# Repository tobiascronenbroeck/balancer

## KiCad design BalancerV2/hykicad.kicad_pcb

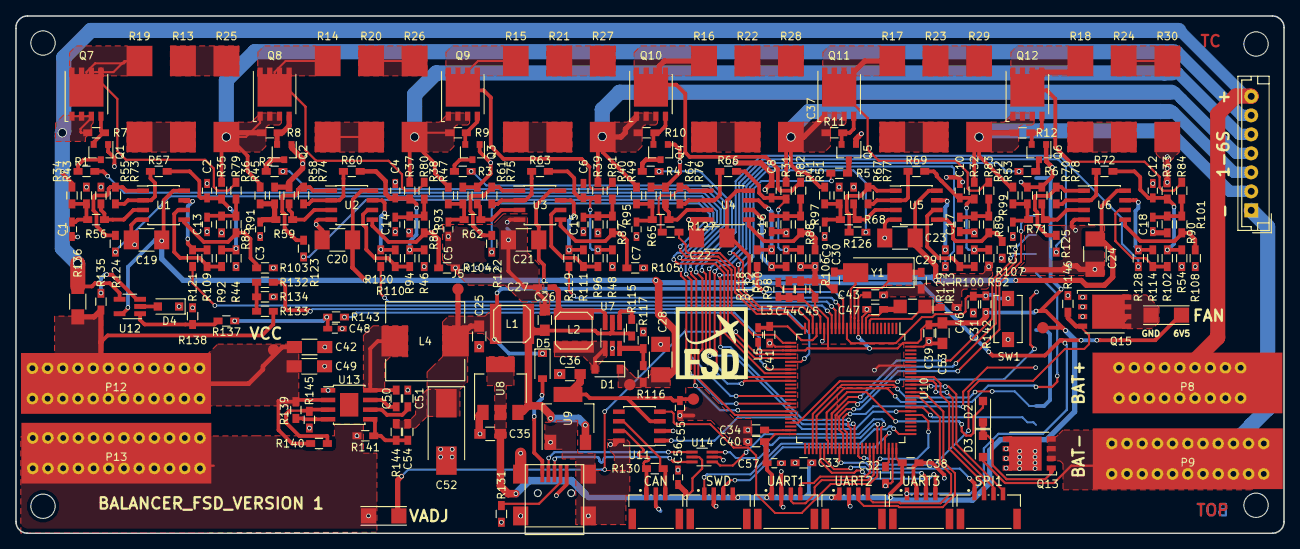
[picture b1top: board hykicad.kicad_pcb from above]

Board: 2 copper layers, 166.9 x 68.1 mm, 264 parts (1 on the bottom side), 177 nets.

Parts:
32.768kHz1: Crystal_Small; Crystal_SMD_MicroCrystal_CC7V-T1A-2pin_3.2x1.5mm_HandSolder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
C1, C2, C3, C4, C5, C6, C7, C8, C9, C10, C11, C12, C13, C14, C15, C16, C17, C18, C27, C48, C55, C56, C57: 100nF; C_0603_HandSoldering
C19, C20, C21, C22, C23, C24, C28: 2.2uF 100V; C_1210_HandSoldering
C25, C26, C35, C36, C53: 4,7uF 16V; R_0805_HandSoldering
C29, C30, C46, C47: 18pF; R_0603_HandSoldering
C31, C33, C34, C37, C38, C39, C40, C41, C43, C45: 100nF; R_0603_HandSoldering
C32: 10uF; R_0603_HandSoldering
C42: 4.7uF 100V X7S; C_1206_HandSoldering
C44: 1uF; R_0603_HandSoldering
C49: 0.1uF 100V X7R; C_1206_HandSoldering
C50: 0.01uF 50V; R_0603_HandSoldering
C51: 1uF 50V; R_0603_HandSoldering
C52: Tantal 100uF 10V; CP_Tantalum_Case-V_EIA-7343-20_Hand
C54: 3.3nF 50V; R_0603_HandSoldering
D1, D5: D; D_SOD-123
D2, D3, D4: D_Schottky; D_SOD-123F
J1, J2, J3, J4, J5: CONN_01X01; Measurement_Point_Round-SMD-Pad_Small
L1, L2: 100uH/4818/0.4A; SELF-WE-TPC_M
L3, L5: 1uH 750mA; C_0603_HandSoldering
L4: 330uF 690mA; Inductor_Wurth_HCI-1040
P1: USB_OTG; USB_Mini-B
P2: CONN_01X03; pel_molex-CM-502386-03
P3, P4, P5, P6, P11: CONN_01X04; pel_molex-CM-502386-04
P7: CONN_01X07; JST_EH_B07B-EH-A_07x2.50mm_Straight
P8: BAT+; 4mmHorizontal
P9, P13: GND; 4mmHorizontal
P10: CONN_01X14; FPC_14
P12: VCC; 4mmHorizontal
P14, P15: CONN_01X02; FPC_2
Q1, Q2, Q3, Q4, Q5, Q6: BC846; SOT-23
Q7, Q8, Q9, Q10, Q11, Q12: PMOS_TDSON; TDSON-8-1_HandSoldering
Q13, Q15: NMOS_TDSON; TDSON-8-1_HandSoldering
R1, R2, R3, R4, R5, R6: 3,3k; R_0603_HandSoldering
R7, R8, R9, R10, R11, R12: 47k; R_0603_HandSoldering
R13, R14, R15, R16, R17, R18, R19, R20, R21, R22, R23, R24, R25, R26, R27, R28, R29, R30: 1R2; SM_3 Pad
R31, R32, R33, R34, R35, R36, R37, R38, R39, R40, R41, R42, R43, R44, R45, R46, R47, R48, R49, R50, R51, R52, R53, R54, R79, R80, R81, R82, R83, R84, R85, R86, R87, R88, R89, R90, R127, R134: 100K; R_0603_HandSoldering
R55, R56, R57, R58, R59, R60, R61, R62, R63, R64, R65, R66, R67, R68, R69, R70, R71, R72, R73, R74, R75, R76, R77, R78, R91, R92, R93, R94, R95, R96, R97, R98, R99, R100, R101, R102, R103, R104, R105, R106, R107, R108, R109, R110, R111, R112, R113, R114, R115, R118, R119, R120, R121, R122, R123, R124, R125, R126, R128, R129, R132, R133, R137, R142, R143, R146: 10K; R_0603_HandSoldering
R116: 123K; R_0603_HandSoldering
R117: 5K1; R_0603_HandSoldering
R130: 120R; R_0603_HandSoldering
R131: OTG Jumper; R_0603_HandSoldering
R135: 100R; R_0603_HandSoldering
R136: 5mR; R_1206_HandSoldering
R138: 5K; R_0603_HandSoldering
R139: 221K; R_0603_HandSoldering
R140: 51.1K; R_0603_HandSoldering
R141: 2.37k; R_0603_HandSoldering
R144: 10k; R_0603_HandSoldering
R145: 10.7K; R_0603_HandSoldering
SW1: SW_PUSH_SMALL_H; SW_SPST_EVQPE1
U1, U2, U3, U4, U5, U6: LM358; SOIC-8_3.9x4.9mm_Pitch1.27mm
U7: MP3216DJ-LF-Z; TSOT-23-6_MK06A_HandSoldering
U8: AP111733; SOT-223
U9: AP111750; SOT-223
U10: STM32F407VGTx; LQFP-100_14x14mm_Pitch0.5mm
U11: TJA1051T; SOIC-8_3.9x4.9mm_Pitch1.27mm
U12: LT6106; SOT-23-5_HandSoldering
U13: LM5017MR; TI_SO-PowerPAD-8
U14: NUF2221W1T2G; SOT-363_SC-70-6_Handsoldering
Y1: 8MHz; Crystal_SMD_0603-2pin_6.0x3.5mm_HandSoldering

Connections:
6,5V: C25.1, C52.1, C54.2, D5.1, J5.1, L1.1, L4.2, P6.1, P14.2, R144.1
32V: C19.1, C20.1, C21.1, C22.1, C23.1, C24.1, C28.1, D1.1, J1.1, R116.2, U1.8, U2.8, U3.8, U4.8, U5.8, U6.8, U12.5
+3V3: C33.1, C35.1, C37.1, C38.1, C39.1, C40.1, C43.2, C53.1, C56.1, C57.1, J4.1, L3.1, L5.1, P3.4, P4.1, P5.1, P10.1, P10.8, R142.1, U8.2, U8.4, U10.11, U10.19, U10.28, U10.50, U10.75, U10.100, U14.5
+5V: C36.1, C55.2, J3.1, U9.4, U11.3
BAT-: D3.2, P7.1, P9.1, Q13.2, Q13.3, Q13.4
CANuC+: P2.1, R130.1, U11.7
CANuC-: P2.3, R130.2, U11.6
CELL1: P7.2, Q12.1, Q12.2, Q12.3, R12.1, R29.1, R32.2, R42.2
CELL2: P7.3, Q11.1, Q11.2, Q11.3, R11.1, R28.1, R31.2, R41.2
CELL3: P7.4, Q10.1, Q10.2, Q10.3, R10.1, R27.1, R39.2, R40.2
CELL4: P7.5, Q9.1, Q9.2, Q9.3, R9.1, R26.1, R37.2, R38.2
CELL5: P7.6, Q8.1, Q8.2, Q8.3, R8.1, R25.1, R35.2, R36.2
CELL6: P7.7, P8.1, Q7.1, Q7.2, Q7.3, R7.1, R34.2, R136.2, U12.4
CS_LCD: P10.3, U10.61
CS_SD: P11.1, U10.60
CS_TOUCH: P10.11, U10.62
Cell1PWM: R1.2, U10.40
Cell2PWM: R2.2, U10.42
Cell3PWM: R3.2, U10.44
Cell4PWM: R4.2, U10.45
Cell5PWM: R5.2, U10.63
Cell6PWM: R6.2, U10.64
D/C_LCD: P10.5, U10.58
DAC1: P15.1, U10.29
ENFAN: Q15.4, R146.1, U10.65
ENGCON: D2.2, U10.57
GND: C1.2, C2.2, C3.2, C4.2, C5.2, C6.2, C7.2, C8.2, C9.2, C10.2, C11.2, C12.2, C13.2, C14.2, C15.2, C16.2, C17.2, C18.2, C19.2, C20.2, C21.2, C22.2, C23.2, C24.2, C25.2, C26.2, C27.1, C28.2, C29.1, C30.1, C31.1, C32.1, C33.2, C34.1, C35.2, C36.2, C37.2, C38.2, C39.2, C40.2, C41.1, C42.2, C43.1, C44.1, C45.1, C46.1, C47.1, C48.1, C49.2, C51.1, C52.2, C53.2, C55.1, C56.2, C57.2, D4.1, P1.5, P1.6, P2.2, P3.2, P4.2, P5.2, P6.2, P10.2, P13.1, P15.2, Q1.1, Q2.1, Q3.1, Q4.1, Q5.1, Q6.1, Q13.5, Q15.1, Q15.2, Q15.3, R30.1, R33.2, R43.2, R44.2, R45.2, R46.2, R47.2, R48.2, R49.2, R50.2, R51.2, R52.2, R53.2, R54.2, R55.1, R58.1, R61.1, R64.1, R67.1, R70.1, R85.2, R86.2, R87.2, R88.2, R89.2, R90.2, R103.2, R104.2, R105.2, R106.2, R107.2, R108.2, R117.1, R131.1, R134.2, R138.1, R141.2, R145.1, R146.2, SW1.1, U1.4, U2.4, U3.4, U4.4, U5.4, U6.4, U7.2, U8.1, U9.1, U10.10, U10.20, U10.27, U10.74, U10.94, U10.99, U11.2, U11.8, U13.1, U14.2
IBATSENSE: C48.2, R137.1, R143.1
IBZ1: R114.1, R128.2, U6.7
IBZ2: R113.1, R129.2, U5.7
IBZ3: R112.1, R118.1, U4.7
IBZ4: R111.1, R119.1, U3.7
IBZ5: R110.1, R120.1, U2.7
IBZ6: R109.1, R121.1, U1.7
unnamed: 32.768kHz1.1, C46.2, U10.8
unnamed: 32.768kHz1.2, C47.2, U10.9
unnamed: C1.1, R34.1, R43.1, R56.2
unnamed: C2.1, R35.1, R44.1, R57.2, R92.2
unnamed: C3.1, R36.1, R45.1, R59.2
unnamed: C4.1, R37.1, R46.1, R60.2, R94.2
unnamed: C5.1, R38.1, R47.1, R62.2
unnamed: C6.1, R39.1, R48.1, R63.2, R96.2
unnamed: C7.1, R40.1, R49.1, R65.2
unnamed: C8.1, R31.1, R50.1, R66.2, R98.2
unnamed: C9.1, R41.1, R51.1, R68.2
unnamed: C10.1, R32.1, R52.1, R69.2, R100.2
unnamed: C11.1, R42.1, R53.1, R71.2
unnamed: C12.1, R33.1, R54.1, R72.2, R102.2
unnamed: C13.1, R79.1, R85.1, R91.2
unnamed: C14.1, R80.1, R86.1, R93.2
unnamed: C15.1, R81.1, R87.1, R95.2
unnamed: C16.1, R82.1, R88.1, R97.2
unnamed: C17.1, R83.1, R89.1, R99.2
unnamed: C18.1, R84.1, R90.1, R101.2
unnamed: C26.1, L1.2, R115.2, U7.5, U8.3, U9.3
unnamed: C27.2, L2.1, U7.6
unnamed: C29.2, U10.12, Y1.1
unnamed: C30.2, U10.13, Y1.2
unnamed: C31.2, R142.2, SW1.2, U10.14
unnamed: C32.2, U10.73
unnamed: C34.2, U10.49
unnamed: C41.2, L5.2, U10.22
unnamed: C44.2, C45.2, L3.2, U10.21
unnamed: C50.1, L4.1, U13.8
unnamed: C50.2, U13.7
unnamed: C51.2, U13.6
unnamed: C54.1, R141.1, R144.2, U13.5
unnamed: D1.2, L2.2, U7.1
unnamed: D2.1, D3.1, Q13.1
unnamed: D4.2, U12.2
unnamed: D5.2, P1.1
unnamed: P1.4, R131.2
unnamed: P14.1, Q15.5
unnamed: Q1.2, Q7.4, R7.2
unnamed: Q1.3, R1.1
unnamed: Q2.2, Q8.4, R8.2
unnamed: Q2.3, R2.1
unnamed: Q3.2, Q9.4, R9.2
unnamed: Q3.3, R3.1
unnamed: Q4.3, R4.1
unnamed: Q5.3, R5.1
unnamed: Q6.3, R6.1
unnamed: Q7.5, R13.2, R79.2
unnamed: Q8.5, R14.2, R80.2
unnamed: Q9.5, R15.2, R81.2
unnamed: Q4.2, Q10.4, R10.2
unnamed: Q10.5, R16.2, R82.2
unnamed: Q5.2, Q11.4, R11.2
unnamed: Q11.5, R17.2, R83.2
unnamed: Q6.2, Q12.4, R12.2
unnamed: Q12.5, R18.2, R84.2
unnamed: R13.1, R19.2
unnamed: R14.1, R20.2
unnamed: R15.1, R21.2
unnamed: R16.1, R22.2
unnamed: R17.1, R23.2
unnamed: R18.1, R24.2
unnamed: R19.1, R25.2
unnamed: R20.1, R26.2
unnamed: R21.1, R27.2
unnamed: R22.1, R28.2
unnamed: R23.1, R29.2
unnamed: R24.1, R30.2
unnamed: R55.2, R56.1, U1.3
unnamed: R57.1, R73.2, U1.2
unnamed: R58.2, R59.1, U2.3
unnamed: R60.1, R74.2, U2.2
unnamed: R61.2, R62.1, U3.3
unnamed: R63.1, R75.2, U3.2
unnamed: R64.2, R65.1, U4.3
unnamed: R66.1, R76.2, U4.2
unnamed: R67.2, R68.1, U5.3
unnamed: R69.1, R77.2, U5.2
unnamed: R70.2, R71.1, U6.3
unnamed: R72.1, R78.2, U6.2
unnamed: R100.1, R113.2, U5.6
unnamed: R101.1, R108.1, U6.5
unnamed: R102.1, R114.2, U6.6
unnamed: R91.1, R103.1, U1.5
unnamed: R93.1, R104.1, U2.5
unnamed: R95.1, R105.1, U3.5
unnamed: R97.1, R106.1, U4.5
unnamed: R99.1, R107.1, U5.5
unnamed: R92.1, R109.2, U1.6
unnamed: R94.1, R110.2, U2.6
unnamed: R96.1, R111.2, U3.6
unnamed: R98.1, R112.2, U4.6
unnamed: R115.1, U7.4
unnamed: R116.1, R117.2, U7.3
unnamed: R118.2, U10.15
unnamed: R119.2, U10.16
unnamed: R120.2, U10.17
unnamed: R121.2, U10.18
unnamed: R122.2, U10.26
unnamed: R123.2, U10.34
unnamed: R124.2, U10.30
unnamed: R125.1, U10.23
unnamed: R126.1, U10.24
unnamed: R127.1, U10.25
unnamed: R128.1, U10.35
unnamed: R129.1, U10.36
unnamed: R132.2, U10.31
unnamed: R135.2, U12.3
unnamed: R137.2, R138.2, U12.1
unnamed: R139.1, U13.4
unnamed: R140.1, R145.2, U13.3
unnamed: R143.2, U10.33
unnamed: U10.81, U11.4
unnamed: U10.82, U11.1
RST_LCD: P10.4, U10.59
SPI1_MISO: P11.3, U10.90
SPI1_MOSI: P11.2, U10.91
SPI1_SCK: P11.4, U10.89
SPI2_MISO: P10.9, P10.13, U10.53
SPI2_MOSI: P10.6, P10.12, U10.54
SPI2_SCK: P10.7, P10.10, U10.47
SWCLK: P3.1, U10.76
SWDIO: P3.3, U10.72
TOUCH_IRQ: P10.14, U10.83
UART1_RX: P4.3, U10.69
UART1_TX: P4.4, U10.68
UART2_RX: P5.3, U10.87
UART2_TX: P5.4, U10.86
UART3_RX: P6.3, U10.56
UART3_TX: P6.4, U10.55
UBATSENSE: R132.1, R133.2, R134.1
USB+: P1.3, U14.6
USB-: P1.2, U14.4
USBuC+: U10.71, U14.1
USBuC-: U10.70, U14.3
UZ1: R78.1, R125.2, U6.1
UZ2: R77.1, R126.2, U5.1
UZ3: R76.1, R127.2, U4.1
UZ4: R75.1, R122.1, U3.1
UZ5: R74.1, R123.1, U2.1
UZ6: R73.1, R124.1, U1.1
VCC: C42.1, C49.1, J2.1, P12.1, R133.1, R135.1, R136.1, R139.2, R140.2, U13.2

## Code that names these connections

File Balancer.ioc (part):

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Mcu.Name=STM32F407V(E-G)Tx
Mcu.Package=LQFP100
Mcu.UserName=STM32F407VGTx
PA0-WKUP.GPIOParameters=GPIO_Label
PA0-WKUP.GPIO_Label=UZ6
PA0-WKUP.Signal=ADCx_IN0
PA1.GPIOParameters=GPIO_Label
PA1.GPIO_Label=UZ5
PA1.Signal=ADCx_IN1
PA10.Mode=Asynchronous
PA10.Signal=USART1_RX
PA11.Mode=Device_Only
PA11.Signal=USB_OTG_FS_DM
PA12.Mode=Device_Only
PA12.Signal=USB_OTG_FS_DP
PA13.Mode=Serial_Wire
PA13.Signal=SYS_JTMS-SWDIO
PA14.Mode=Serial_Wire
PA14.Signal=SYS_JTCK-SWCLK
PA2.GPIOParameters=GPIO_Label
PA2.GPIO_Label=UZ4
PA2.Signal=ADCx_IN2
PA3.GPIOParameters=GPIO_Label
PA3.GPIO_Label=UZ3
PA3.Signal=ADCx_IN3
PA4.GPIOParameters=GPIO_Label
PA4.GPIO_Label=DAC1
PA4.Signal=COMP_DAC1_group
PA5.GPIOParameters=GPIO_Label
PA5.GPIO_Label=UZ1
PA5.Signal=ADCx_IN5
PA6.GPIOParameters=GPIO_Label
PA6.GPIO_Label=UBATSENSE
PA6.Signal=ADCx_IN6
PA9.Mode=Asynchronous
PA9.Signal=USART1_TX
PB0.GPIOParameters=GPIO_Label
PB0.GPIO_Label=IBZ6
PB0.Signal=ADCx_IN8
PB1.GPIOParameters=GPIO_Label
PB1.GPIO_Label=IBZ5
PB1.Signal=ADCx_IN9
PB10.Mode=Full_Duplex_Master
PB10.Signal=SPI2_SCK
PB14.Mode=Full_Duplex_Master
PB14.Signal=SPI2_MISO
PB15.Mode=Full_Duplex_Master
PB15.Signal=SPI2_MOSI
PB3.Mode=Full_Duplex_Master
PB3.Signal=SPI1_SCK
PB4.Mode=Full_Duplex_Master
PB4.Signal=SPI1_MISO
PB5.Mode=Full_Duplex_Master
PB5.Signal=SPI1_MOSI
PC0.GPIOParameters=GPIO_Label
PC0.GPIO_Label=IBZ4
PC0.Signal=ADCx_IN10
PC1.GPIOParameters=GPIO_Label
PC1.GPIO_Label=IBZ3
PC1.Signal=ADCx_IN11
PC14-OSC32_IN.Mode=LSE-External-Oscillator
PC14-OSC32_IN.Signal=RCC_OSC32_IN
PC15-OSC32_OUT.Mode=LSE-External-Oscillator
PC15-OSC32_OUT.Signal=RCC_OSC32_OUT
PC2.GPIOParameters=GPIO_Label
PC2.GPIO_Label=IBZ2
PC2.Signal=ADCx_IN12
PC3.GPIOParameters=GPIO_Label
PC3.GPIO_Label=IBZ1
PC3.Signal=ADCx_IN13
PC4.GPIOParameters=GPIO_Label
PC4.GPIO_Label=IBATSENSE
PC4.Signal=ADCx_IN14
PC5.GPIOParameters=GPIO_Label
PC5.GPIO_Label=UZ2
PC5.Signal=ADCx_IN15
PC6.GPIOParameters=GPIO_PuPd,GPIO_Label
PC6.GPIO_Label=Cell5PWM
PC6.GPIO_PuPd=GPIO_PULLDOWN
PC6.Signal=S_TIM3_CH1
PC7.GPIOParameters=GPIO_PuPd,GPIO_Label
PC7.GPIO_Label=Cell6PWM
PC7.GPIO_PuPd=GPIO_PULLDOWN
PC7.Signal=S_TIM3_CH2
PC8.GPIOParameters=GPIO_PuPd,GPIO_Label
PC8.GPIO_Label=ENFAN
PC8.GPIO_PuPd=GPIO_PULLDOWN
PC8.Signal=S_TIM3_CH3
PD0.Mode=Master
PD0.Signal=CAN1_RX
PD1.Mode=Master
PD1.Signal=CAN1_TX
PD10.GPIOParameters=GPIO_Label
PD10.GPIO_Label=ENGCON
PD10.Signal=GPIO_Output
PD11.GPIOParameters=GPIO_Label
PD11.GPIO_Label=D/C_LCD
PD11.Signal=GPIO_Output
PD12.GPIOParameters=GPIO_Label
PD12.GPIO_Label=RST_LCD
PD12.Signal=GPIO_Output
PD13.GPIOParameters=GPIO_Label
PD13.GPIO_Label=CS_SD
PD13.Signal=GPIO_Output
PD14.GPIOParameters=GPIO_Label
PD14.GPIO_Label=CS_LCD
PD14.Signal=GPIO_Output
PD15.GPIOParameters=GPIO_Label
PD15.GPIO_Label=CS_TOUCH
PD15.Signal=GPIO_Output
PD2.GPIOParameters=GPIO_Label
PD2.GPIO_Label=Touch_IRQ
PD2.Signal=GPIO_Input
PD5.Mode=Asynchronous
PD5.Signal=USART2_TX
PD6.Mode=Asynchronous
PD6.Signal=USART2_RX
PD8.Mode=Asynchronous
PD8.Signal=USART3_TX
PD9.Mode=Asynchronous
PD9.Signal=USART3_RX
PE11.GPIOParameters=GPIO_PuPd,GPIO_Label
PE11.GPIO_Label=Cell2PWM
PE11.GPIO_PuPd=GPIO_PULLDOWN
PE11.Signal=S_TIM1_CH2
PE13.GPIOParameters=GPIO_PuPd,GPIO_Label
PE13.GPIO_Label=Cell3PWM
PE13.GPIO_PuPd=GPIO_PULLDOWN
PE13.Signal=S_TIM1_CH3
PE14.GPIOParameters=GPIO_PuPd,GPIO_Label
PE14.GPIO_Label=Cell4PWM
PE14.GPIO_PuPd=GPIO_PULLDOWN
PE14.Signal=S_TIM1_CH4
PE9.GPIOParameters=GPIO_PuPd,GPIO_Label
PE9.GPIO_Label=Cell1PWM
PE9.GPIO_PuPd=GPIO_PULLDOWN
PE9.Signal=S_TIM1_CH1
PH0-OSC_IN.Mode=HSE-External-Oscillator
PH0-OSC_IN.Signal=RCC_OSC_IN
PH1-OSC_OUT.Mode=HSE-External-Oscillator
PH1-OSC_OUT.Signal=RCC_OSC_OUT
RCC.HSE_VALUE=8000000
RCC.SYSCLKFreq_VALUE=168000000
RCC.SYSCLKSource=RCC_SYSCLKSOURCE_PLLCLK
board=Balancer

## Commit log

2017-10-10 Init Balancer HAL
2017-10-11 ST Firmware Update / improved UART Write Method
2017-10-11 Adding DMA Support for ADC Conversion
2017-10-11 omit hal adc start for the moment
2017-10-13 Set Sampling Loops for each ADC Channel to 144 Starting ADC_DMA
2017-10-13 Added Voltage Calculation for ADCs
2017-10-15 Added ADC Reading
2017-10-15 fixes
2017-10-15 Added PWM Output
2017-10-16 Added Battery GND Connection
2017-10-16 Added internal Temp Sensor Conversion & Rearranged ADC order
2017-10-17 Added calibration mode to ADC Vref rail
2017-10-17 First Calibration & Voltage to UART
2017-10-17 Calibration of UBat ADC
2017-10-18 1. Calibration for all Channels
2017-11-02 Added DAC DMA Init
2018-01-04 Added Voltage Output
2018-01-10 improved DAC DCDC Controller
2018-01-17 Added Schematics
2018-01-17 Improved ADC Averaging & Circuit Adjustments
